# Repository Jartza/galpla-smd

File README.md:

# Commodore 64 GAL-PLA SMD-version

Commodore 64 PLA replacement using GAL20V8B 28-pin PLCC chips. Based on [PLA20V8](https://www.freepascal.org/~daniel/c64pla/) by Daniël Mantione. Published under permission from Daniël.

This version uses 2 pieces of GAL20V8B chips in 28-pin PLCC package. Due to size constraints, soldering the chips is best done by hot air or hot plate, either using solder paste or tinning the pads and using flux. Fuse map is the same as in DIP-version. In the middle of the board there is a footprint for 0603 (optional) bypass capacitor, 0.1-0.22uF.

Fuse map is unchanged, use original Fuse map from [Daniël's site](https://www.freepascal.org/~daniel/c64pla/)

If you want to order PCBs from PCBWay, follow [this link](https://www.pcbway.com/project/shareproject/Commodore_64_PLA_replacement_d4be5faf.html)

This repository includes the Eagle-files for PCB, and also generated Gerbers.

&nbsp;&nbsp;&nbsp;&nbsp;&nbsp;

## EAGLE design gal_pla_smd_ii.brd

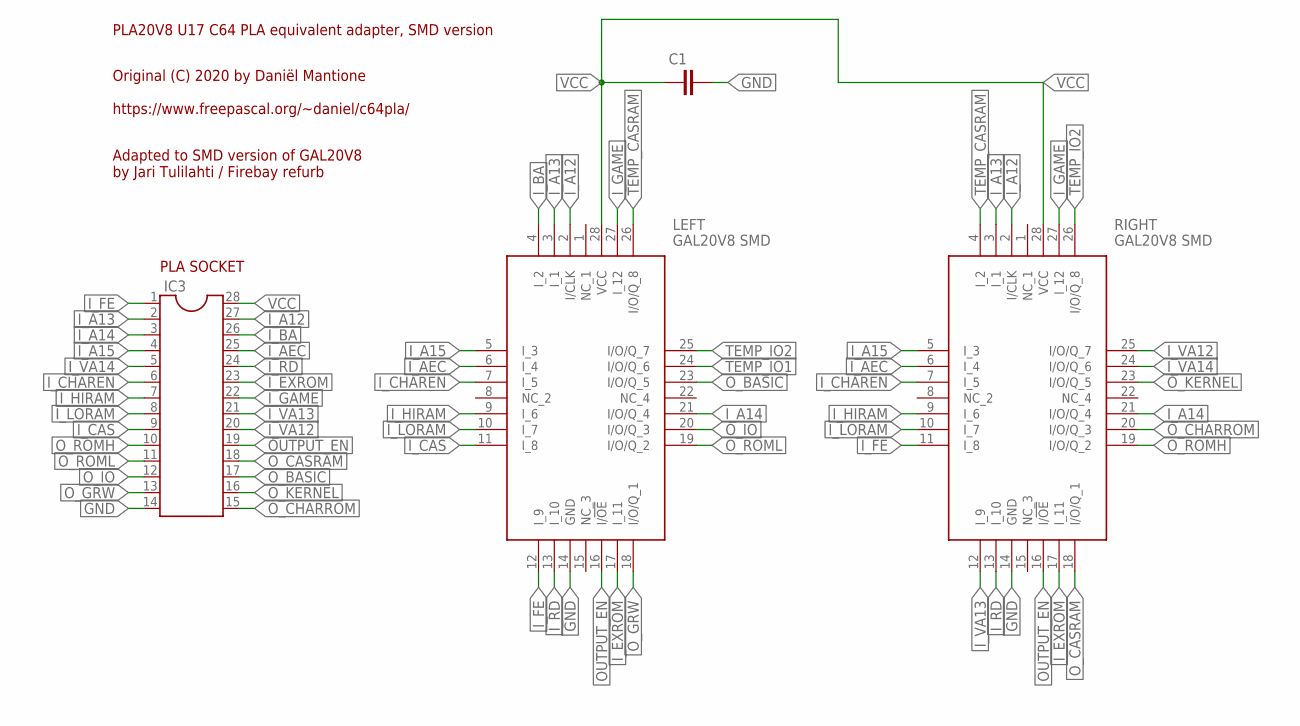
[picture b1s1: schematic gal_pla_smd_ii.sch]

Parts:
C1: CAP0603-CAP; 0603-CAP
IC3: DIL28; DIL28-6
LEFT: GAL20V8 SMD; PLCC127P1245X1245X457-28N
RIGHT: GAL20V8 SMD; PLCC127P1245X1245X457-28N

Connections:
GND: C1.2, IC3.14, LEFT.14 (GND), RIGHT.14 (GND)
I_A12: IC3.27, LEFT.2 (I/CLK), RIGHT.2 (I/CLK)
I_A13: IC3.2, LEFT.3 (I_1), RIGHT.3 (I_1)
I_A14: IC3.3, LEFT.21 (I/O/Q_4), RIGHT.21 (I/O/Q_4)
I_A15: IC3.4, LEFT.5 (I_3), RIGHT.5 (I_3)
I_AEC: IC3.25, LEFT.6 (I_4), RIGHT.6 (I_4)
I_BA: IC3.26, LEFT.4 (I_2)
I_CAS: IC3.9, LEFT.11 (I_8)
I_CHAREN: IC3.6, LEFT.7 (I_5), RIGHT.7 (I_5)
I_EXROM: IC3.23, LEFT.17 (I_11), RIGHT.17 (I_11)
I_FE: IC3.1, LEFT.12 (I_9), RIGHT.11 (I_8)
I_GAME: IC3.22, LEFT.27 (I_12), RIGHT.27 (I_12)
I_HIRAM: IC3.7, LEFT.9 (I_6), RIGHT.9 (I_6)
I_LORAM: IC3.8, LEFT.10 (I_7), RIGHT.10 (I_7)
I_RD: IC3.24, LEFT.13 (I_10), RIGHT.13 (I_10)
I_VA12: IC3.20, RIGHT.25 (I/O/Q_7)
I_VA13: IC3.21, RIGHT.12 (I_9)
I_VA14: IC3.5, RIGHT.24 (I/O/Q_6)
OUTPUT_EN: IC3.19, LEFT.16 (I/!OE), RIGHT.16 (I/!OE)
O_BASIC: IC3.17, LEFT.23 (I/O/Q_5)
O_CASRAM: IC3.18, RIGHT.18 (I/O/Q_1)
O_CHARROM: IC3.15, RIGHT.20 (I/O/Q_3)
O_GRW: IC3.13, LEFT.18 (I/O/Q_1)
O_IO: IC3.12, LEFT.20 (I/O/Q_3)
O_KERNEL: IC3.16, RIGHT.23 (I/O/Q_5)
O_ROMH: IC3.10, RIGHT.19 (I/O/Q_2)
O_ROML: IC3.11, LEFT.19 (I/O/Q_2)
TEMP_CASRAM: LEFT.26 (I/O/Q_8), RIGHT.4 (I_2)
TEMP_IO1: LEFT.24 (I/O/Q_6)
TEMP_IO2: LEFT.25 (I/O/Q_7), RIGHT.26 (I/O/Q_8)
VCC: C1.1, IC3.28, LEFT.28 (VCC), RIGHT.28 (VCC)

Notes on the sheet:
PLA SOCKET
PLA20V8 U17 C64 PLA equivalent adapter, SMD version
Original (C) 2020 by Daniël Mantione https://www.freepascal.org/~daniel/c64pla/
Adapted to SMD version of GAL20V8 by Jari Tulilahti / Firebay refurb

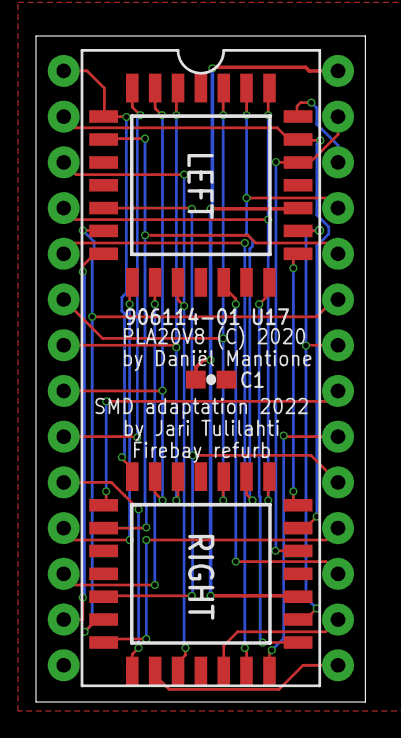
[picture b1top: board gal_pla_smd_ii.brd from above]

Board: 2 copper layers, 18.3 x 37.0 mm, 4 parts (0 on the bottom side), 30 nets.

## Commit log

2022-09-20 Add images
2022-09-20 Update imgae
2022-09-20 Update image
2022-10-27 Update to bigger pads for easier hand-soldering
2022-10-27 Update gerbers
2022-11-19 Update to latest

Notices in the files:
gal_pla_smd_ii.brd:
PLA20V8 (C) 2020
parts and their libraries:
SparkFun-Passives: Licensing: Creative Commons ShareAlike 4.0 International - https://creativecommons.org/licenses/by-sa/4.0
